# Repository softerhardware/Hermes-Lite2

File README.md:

#Hermes-Lite Ver2 Beta5 Compact Transceiver firmware
[_VU2ZAZ's HL2 Companion board_](https://github.com/bnamnaidu/HL2-Companion-board-codec-and-Filter-)

##Based on the official 20180106 firmware.

##Iambic keyer and audio codec (sidetone)
- [_Keyer function_](https://github.com/ji1udd/Hermes-Lite/blob/6M/audiocodec/docs/Keyer_Sequece_and_setting.pdf)
- Mic gain (AK4951) : Normal 18dB, Boost 30dB
- Enable SPEAKER : [_Re-use "Random"_](https://github.com/ji1udd/Hermes-Lite2/blob/CompactTRX/compact-trx/Keyer_AK4951/docs/Speaker_Setting.jpg) on OpenHPSDR protocol.

##HL2 filter (1 HPF, 6 LPFs) control
- [_Alex / Apollo auto filter mode_](https://github.com/ji1udd/Hermes-Lite2/blob/CompactTRX/compact-trx/TX_RX_Filter/docs/Filter_Setting.jpg) ; HPF and LPFs are switched according to TX and multi RXs frequencies.
- Alex manual filter mode ; This mode is not supported by piHPSDR, but supported by [_PowerSDR_](CTRX_HL2b5/docs/PowerSDR_ALEX_ManualFilter_setting_for_Jims_Filter.jpg).
- Short switch latency for CW keyer operation.
- HPF is bypassed during TX.

##External amplifier band control
- Send TX frequency with Elecraft serial command "FA(VFO A frequency)" to ExtAMP.
- UART 9600bps
- Tested with HARDROCK-50
- UART RxD is not used.

##External ATU control
- Enable ATU : Use [_"Apollo auto tune"_](https://github.com/ji1udd/Hermes-Lite2/blob/CompactTRX/compact-trx/powercontrol/docs/ATU_Setting.jpg) on OpenHPSDR protocol.
- Send START trigger to ATU (like Start SW), Receive STATUS from ATU (like Tuning LED).
- [_Control sequence_](https://github.com/ji1udd/Hermes-Lite2/blob/CompactTRX/compact-trx/powercontrol/docs/ATU_timing_chart.jpg)
- Tested with ICOM AH-4

##LED Ports
- The function is automatically selected by ExtAMP/ExtATU interface circuit installation on board.

##Others
- Embedded PA is always enabled for a stand alone transceiver.

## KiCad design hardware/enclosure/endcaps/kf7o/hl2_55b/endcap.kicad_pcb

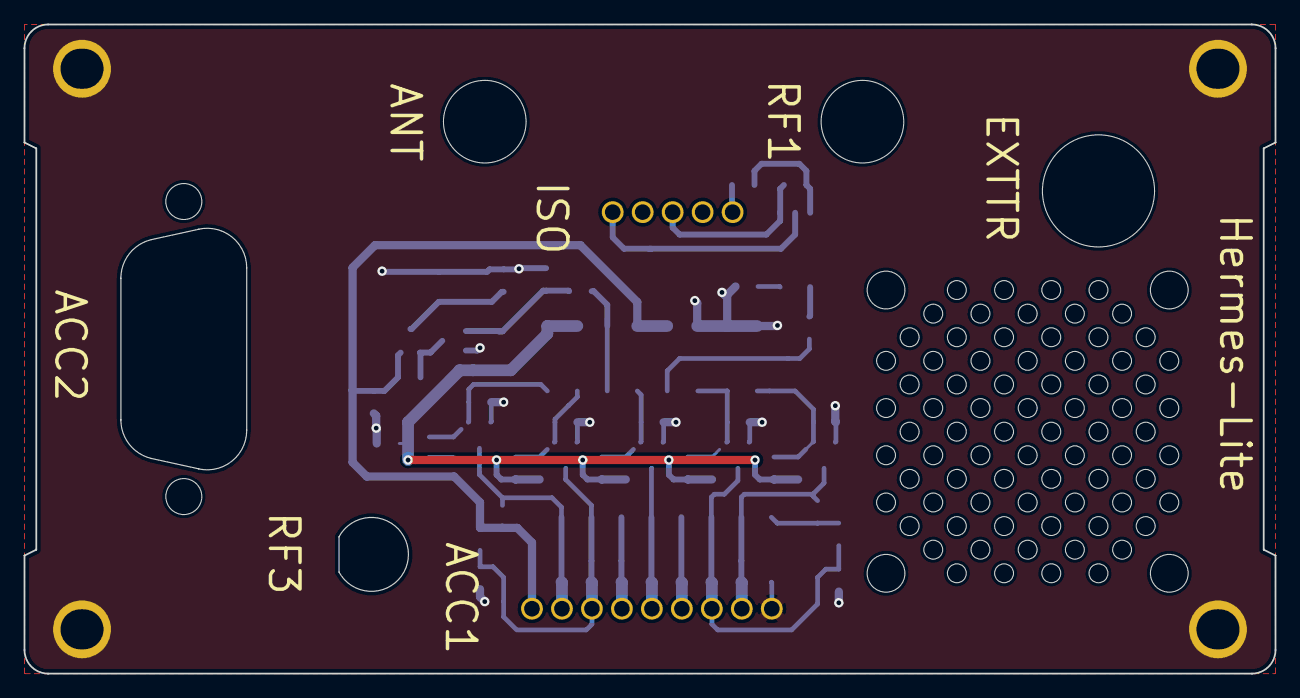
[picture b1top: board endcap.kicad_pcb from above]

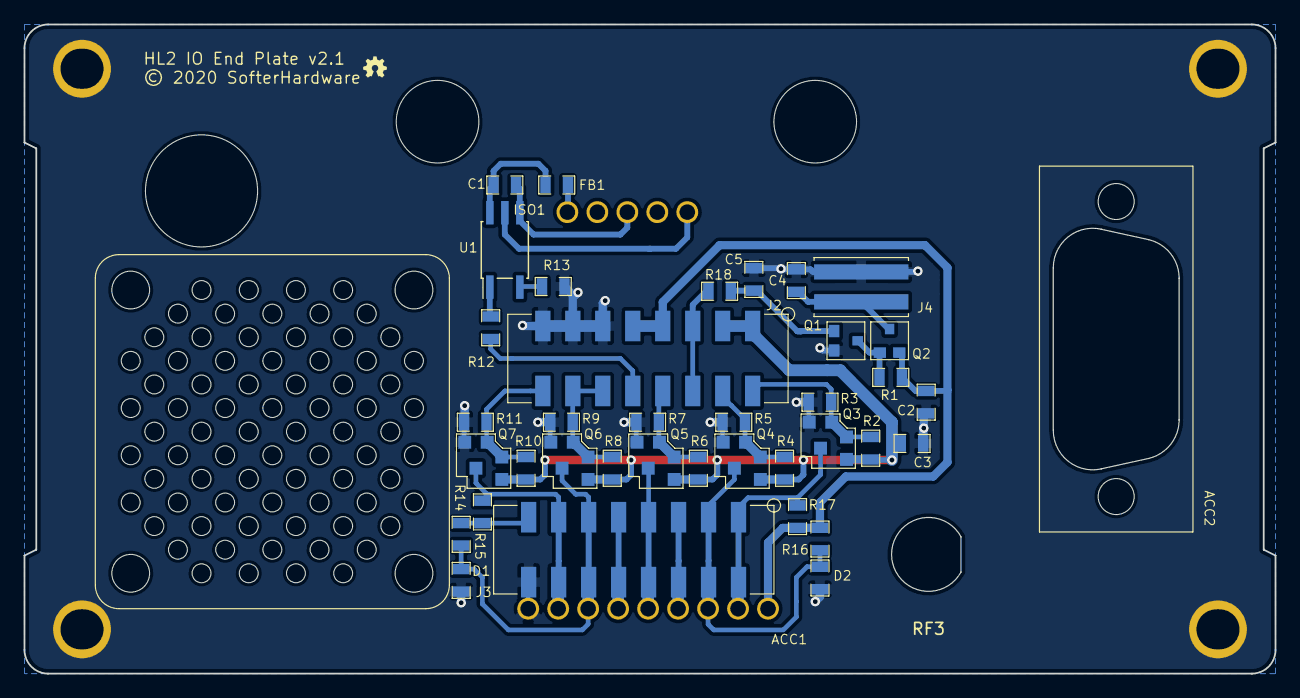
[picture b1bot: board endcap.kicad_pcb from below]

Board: 2 copper layers, 106.0 x 55.0 mm, 45 parts (41 on the bottom side), 27 nets.

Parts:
ACC1: Terminal Block; terminal_block
ACC2: DB9; db9inside
C1, C2, C3, C4, C5: 0.1uF; SMD-0805
D1, D2: 1N4148; SMD-0805
FB1: Ferrite_Bead_Small; SMD-0805
ISO1: Terminal Block; terminal_block5
J2, J3: Male Header; male_header
J4: Fan; male_header_2
MH1, MH2, MH3, MH4: 3mm; mh3mm
Q1: DTC144E; SOT23_3
Q2: IRLML6402; SOT23_3
Q3, Q4, Q5, Q6, Q7: MULTIFET; 3sot3_3
R1, R2, R3, R4, R5, R6, R7, R8, R9, R10, R11, R14, R15, R16, R17: 10K; SMD-0805
R12, R18: 1K; SMD-0805
R13: 680; SMD-0805
RF3: SMA; sma_panel
U1: ACPL-M21L-000E; SO-5_4.4x3.6mm_P1.27mm

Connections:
GNDS: ACC1.9, C2.1, C3.2, C4.1, C5.1, D1.2, D2.2, J2.11, J2.13, J2.15, J3.16, J4.2, MH1.1, MH2.1, MH3.1, MH4.1, Q1.2, Q3.2, Q4.2, Q5.2, Q6.2, Q7.2, R3.2, R5.2, R7.2, R9.2, R11.2, R13.2
ISOIN: J2.10, R12.2
unnamed: ACC1.2, J3.1, J3.2, Q3.3, R17.2
unnamed: ACC1.3, D2.1, J3.3, J3.4, Q4.3, R16.2
unnamed: ACC1.4, J3.5, J3.6
unnamed: ACC1.5, J3.7, J3.8, Q5.3
unnamed: ACC1.6, J3.9, J3.10
unnamed: ACC1.7, D1.1, J3.11, J3.12, Q6.3, R15.1
unnamed: ACC1.8, J3.13, J3.14, Q7.3, R14.1
unnamed: C1.1, FB1.2, U1.6
unnamed: C1.2, ISO1.3, U1.4
unnamed: C4.2, J4.1, Q2.3
unnamed: C5.2, Q1.1, R18.2
unnamed: FB1.1, ISO1.1
unnamed: ISO1.5, U1.5
unnamed: J2.2, Q3.1, R2.2, R3.1
unnamed: J2.4, Q4.1, R4.2, R5.1
unnamed: J2.5, J2.6, R18.1
unnamed: J2.8, Q5.1, R6.2, R7.1
unnamed: J2.12, J2.14, Q6.1, R8.2, R9.1
unnamed: J2.16, Q7.1, R10.2, R11.1
unnamed: J3.15, R14.2, R15.2
unnamed: Q1.3, Q2.1, R1.2
unnamed: R12.1, U1.1
unnamed: R13.1, U1.3
VSUP: ACC1.1, C2.2, J2.7, J2.9, Q2.2, R1.1, R16.1, R17.1
Vlvds: C3.1, J2.1, J2.3, Q3.4, Q4.4, Q5.4, Q6.4, Q7.4, R2.1, R4.1, R6.1, R8.1, R10.1

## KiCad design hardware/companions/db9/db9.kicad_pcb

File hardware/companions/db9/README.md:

# BOM

The BOM below lists possible options for the DB9 adapter board. The builder should choose what components they need to buy and install.

| Reference | Quantity | Component |
| --------- | -------- | --------- |
| J3 | 1 | [DB-9 male](https://www.digikey.com/product-detail/en/edac-inc/627-009-220-047/151-1197-ND/1298747) |
| Q1, Q2 | 2 | [BSS138](https://www.digikey.com/product-detail/en/micro-commercial-co/BSS138W-TP/BSS138W-TPMSCT-ND/6616168) |
| R1, R2 | 2 | [10K 0805](https://www.digikey.com/product-detail/en/yageo/RC0805FR-0710KL/311-10.0KCRCT-ND/730482) |
| J1, J2, J4 | 1 | [5x2 male header](https://www.digikey.com/product-detail/en/sullins-connector-solutions/PRPC005DAAN-RC/S2011EC-05-ND/2775289) |

# Assembly

Please refer to the [schematic](db9.pdf) during assembly. Please refer to the HR50 interface notes found on the [IO wiki page](https://github.com/softerhardware/Hermes-Lite2/wiki/IO#io-boards) for details on how to use this with the HR50.

Below is a picture of an assembled DB-9 IO board. Only one of the level shifter channels is installed, TX on pin 3 of the DB-9. This is all the that HR50 requires. The other level shifter can be installed if RX is required.

This assembly assumes a crossover cable. Install TX on the channel to the DB-9 pin 2 if a straight through cable is used.

The level shifter portion of the PCB can be broken off and jumpers to extra IO channels on the end plate can be used used instead. It is recommended to use the level shifters on the small DB-9 IO board, and the option to break the board may be removed in the future.

## Connection Diagram

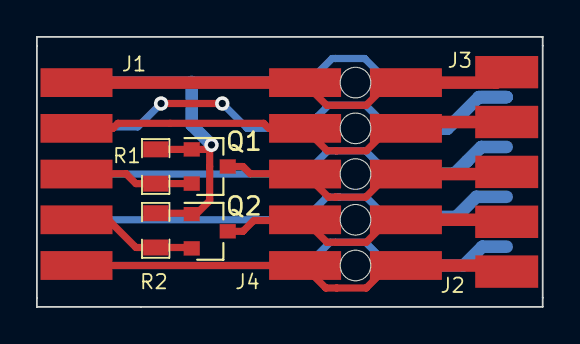
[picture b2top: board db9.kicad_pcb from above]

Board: 2 copper layers, 28.1 x 15.0 mm, 9 parts (0 on the bottom side), 12 nets.

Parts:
B1: break10
J1, J2, J4: edge10
J3: DB9_Male; db9edge
Q1, Q2: BSS138; SOT-23
R1, R2: 10K; SMD-0805

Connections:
GNDS: J1.5, J2.5, J3.5, J4.5
unnamed: J1.1, J2.1, J3.1, J4.1
unnamed: J1.2, Q2.2, R2.2
unnamed: J1.3, Q1.2, R1.2
unnamed: J1.4, J2.4, J3.4, J4.4
unnamed: J1.6, J2.6, J3.6, J4.6
unnamed: J1.7, J2.7, J3.7, J4.7
unnamed: J1.8, J2.8, J3.8, J4.8
unnamed: J1.9, J2.9, J3.9, J4.9
unnamed: J2.2, J3.2, J4.2, Q2.3
unnamed: J2.3, J3.3, J4.3, Q1.3
VCC: J1.10, J2.10, J4.10, Q1.1, Q2.1, R1.1, R2.1

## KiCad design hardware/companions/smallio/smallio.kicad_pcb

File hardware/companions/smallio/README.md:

# BOM

The BOM below lists possible options for IO jumper board. The builder should choose what components they need to buy and install.

| Reference | Quantity | Component |
| --------- | -------- | --------- |
| DB1 | 1 | [5x2 male header 2.54mm](https://www.digikey.com/product-detail/en/sullins-connector-solutions/PRPC005DAAN-RC/S2011EC-05-ND) |
| DB17 | 1 | [4x1 male header 2.54mm](https://www.digikey.com/product-detail/en/w-rth-elektronik/61300411121/732-5317-ND) |
| U1 | 1 | [MCP23008T-E-SS](https://www.digikey.com/product-detail/en/microchip-technology/MCP23008T-E-SS/MCP23008T-E-SSCT-ND) |
| C1 | 1 | [0.1uF 0805](https://www.digikey.com/product-detail/en/kemet/C0805C104Z5VACTU/399-1177-1-ND/411452) |
| J1, J2 | 2 | [0Ohm 0805](https://www.digikey.com/product-detail/en/yageo/RC0805JR-070RL/311-0.0ARCT-ND) |

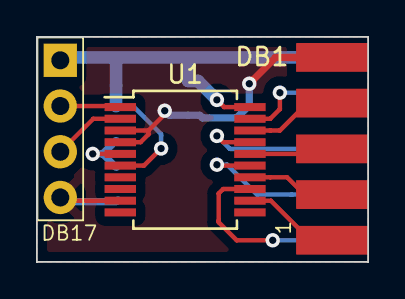
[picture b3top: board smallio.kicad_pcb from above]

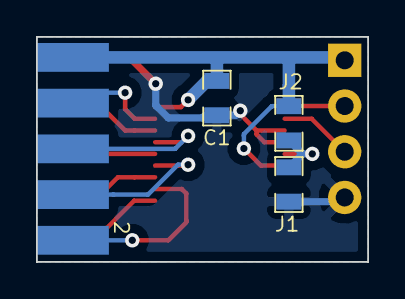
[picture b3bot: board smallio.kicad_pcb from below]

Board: 2 copper layers, 18.4 x 12.5 mm, 6 parts (3 on the bottom side), 13 nets.

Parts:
C1: 0.1uF; SMD-0805
DB1: IO10; edge10_alt
DB17: RFD4d; 4x1
J1, J2: 0; SMD-0805
U1: MCP23008-E_SS; SSOP-20_5.3x7.2mm_P0.65mm

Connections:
GNDS: C1.1, DB1.9, DB17.4, J1.2, U1.3, U1.4, U1.9
unnamed: DB1.1, U1.12
unnamed: DB1.2, U1.13
unnamed: DB1.3, U1.14
unnamed: DB1.4, U1.15
unnamed: DB1.5, U1.16
unnamed: DB1.6, U1.17
unnamed: DB1.7, U1.18
unnamed: DB1.8, U1.19
unnamed: DB17.2, U1.1
unnamed: DB17.3, U1.2
unnamed: J1.1, J2.2, U1.5
VCC: C1.2, DB1.10, DB17.1, J2.1, U1.6, U1.20

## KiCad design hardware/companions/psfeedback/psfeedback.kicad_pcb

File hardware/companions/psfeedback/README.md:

# BOM

The BOM below lists possible options for PureSignal feedback board. The builder should choose what components they need to buy and install.

| Reference | Quantity | Component |
| --------- | -------- | --------- |
| RF1 | 1 | [Edge Launch SMA](https://www.digikey.com/product-detail/en/adam-tech/RF2-04A-T-00-50-G/2057-RF2-04A-T-00-50-G-ND) |
| R1 | 1 | [0Ohm 0805](https://www.digikey.com/product-detail/en/yageo/RC0805JR-070RL/311-0.0ARCT-ND) |
| R2 | 1 | [49.9 0805](https://www.digikey.com/product-detail/en/yageo/RC0805FR-0749R9L/311-49.9CRCT-ND) |
| R3 | 1 | [470 0805](https://www.digikey.com/product-detail/en/yageo/RC0805FR-07470RL/311-470CRCT-ND) |
| R4 | 1 | [1K 0805](https://www.digikey.com/product-detail/en/yageo/RC0805FR-071KL/311-1.00KCRCT-ND) |

# Assembly

Please refer to the [schematic](psfeedback.pdf) during assembly. 

Below is a picture of an assembled PureSignal feedback board soldered on to the HL2/N2ADR jumper board. The components installed are as per the schematic, but experimentation may be necessary to determine the best values. The PCB supports pi and t attenuator configurations. 
[Pi Calculator](https://chemandy.com/calculators/matching-pi-attenuator-calculator.htm)
[T Calculator](https://chemandy.com/calculators/matching-t-attenuator-calculator.htm)

Note that the PCB only connects to one pin on the HL2/N2ADR jumper board. This is so that the connection between the two pins on the HL2/N2ADR jumper board can be drilled open so that less "wire" is hanging off of this line. This can only be done if the feedback board is installed so that it hangs out towards T3. If installed to hang out towards the N2ADR board, then the two pins on the HL2/N2ADR jumper board must remain connected.

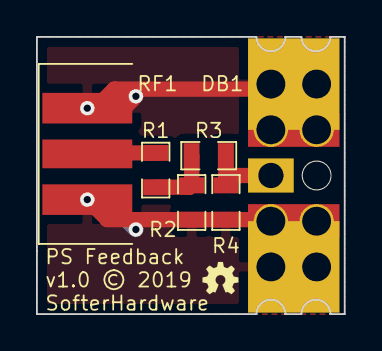
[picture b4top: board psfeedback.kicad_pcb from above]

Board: 2 copper layers, 17.1 x 15.4 mm, 6 parts (0 on the bottom side), 4 nets.

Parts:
DB1: RFD2b; psfeedback
R1: 0; SMD-0805
R2: 50; SMD-0805
R3: 470; SMD-0805
R4: 1K; SMD-0805
RF1: BNC; SMAEDGE

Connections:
GNDS: DB1.2, R2.2, R4.2, RF1.2
unnamed: DB1.1, R3.1, R4.1
unnamed: R1.1, R2.1, R3.2
unnamed: R1.2, RF1.1

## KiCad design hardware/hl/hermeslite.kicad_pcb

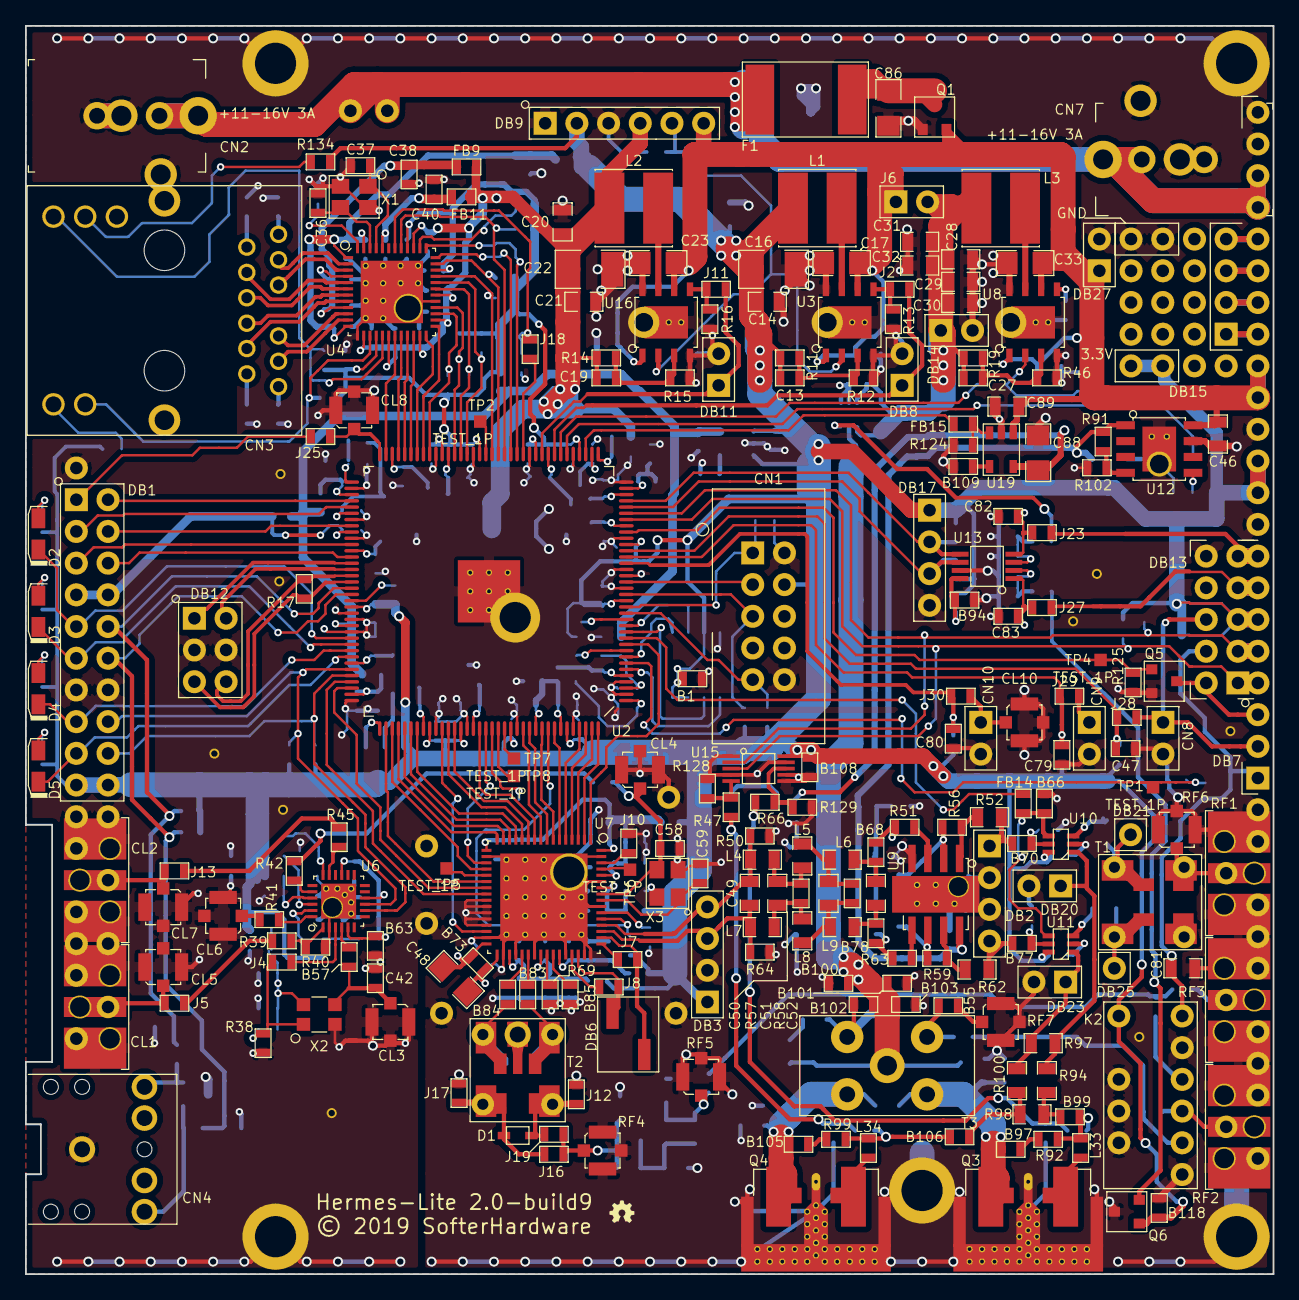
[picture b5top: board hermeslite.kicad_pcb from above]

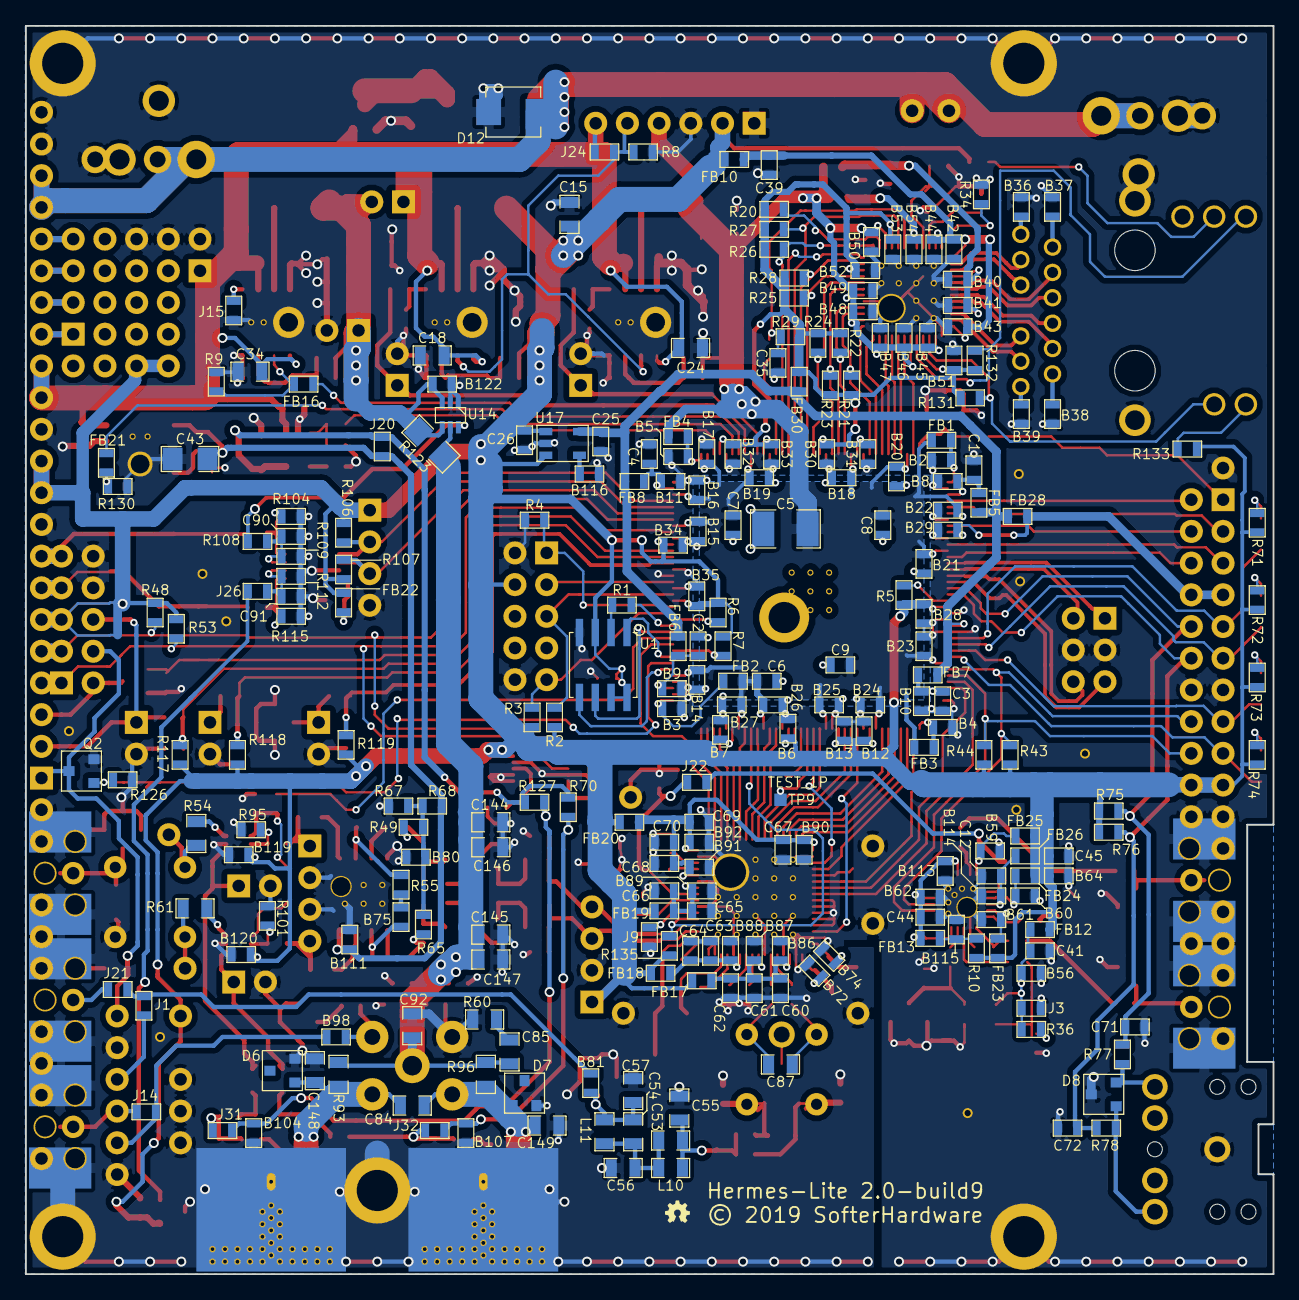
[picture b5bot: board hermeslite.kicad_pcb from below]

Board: 4 copper layers, 99.9 x 100.0 mm, 488 parts (246 on the bottom side), 274 nets.

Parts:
B1, B2, B3, B4, B5, B6, B7, B8, B9, B10, B11, B12, B13, B14, B15, B16, B17, B18, B19, B20, B21, B22, B23, B24, B25, B26, B27, B28, B29, B30, B31, B32, B33, B34, B35, B36, B37, B38, B39, B40, B41, B42, B43, B44, B45, B46, B47, B48, B49, B50, B51, B52, B53, B54, B55, B56, B57, B59, B60, B61, B62, B63, B64, B66, B68, B70, B72, B73, B74, B75, B77, B78, B80, B81, B83, B84, B85, B86, B87, B88, B89, B90, B91, B92, B94, B97, B98, B99, B100, B101, B102, B103, B104, B105, B106, B107, B108, B109, B111, B113, B114, B115, B116, B118, B119, B120, B122: 0.1uF; SMD-0603
C1, C2, C3, C4, C6, C7, C8, C9, C12, C25, C35, C38, C39, C40, C41, C44, C45, C62, C64, C66, C70: 10uF; SMD-0603
C5, C16, C22: 100uF; SMD-1210
C13, C19, C27, C82, C83, C90, C91: 4.7nF; SMD-0603
C14, C15, C20, C21, C28, C29, C30, C31, C32, C92: 22uF; SMD-0805
C17, C23, C33, C43, C48, C86, C88: 10uF; SMD-1206
C18, C24, C34: 4.7uF; SMD-0805
C26, C47, C60, C61, C63, C65, C67, C68, C69, C71, C72, C79, C80: 1uF; SMD-0603
C36, C37, C58, C59: 15pF; SMD-0603
C42: DNI; SMD-0603
C46, C89, C144, C145, C146, C147: 1uF; SMD-0805
C49: 75pF; SMD-0805
C50: 150pF; SMD-0805
C51: 160pF; SMD-0805
C52, C57, C81: 100pF; SMD-0805
C53, C54, C55: 10pF; SMD-0805
C56: 180pF; SMD-0805
C84: 390pF; SMD-0805
C85, C148, C149: 270pF; SMD-0805
C87: 8.2pF; SMD-0805
CL1, CL2: SMA; SMAEDGE_TH_L
CL3, CL4, CL5, CL6, CL7, CL8, CL10: uFL; UFL
CN1: USBBlaster2; USBBLASTER
CN2, CN7: PS; PWRBARREL2
CN3: MagJack; MAGJACK
CN4: STEREO
CN8, CN9, CN10: RFD2b; 2x1
D1: TVS; SOD323
D2, D3, D4, D5: Led_Small; LEDn
D6, D7: DNI; SOT23_3
D8: SM05; SOT23_3
D12: SMBJ18CA; smbj18ca
DB1: IO20; 10x2
DB2, DB3: RFD4d; 4x1
DB6: RFD2b; 2x1smt
DB7: IO22; 22x1
DB8, DB11, DB14, DB20, DB23, DB27: RFD2b; 2x1
DB9: IO6b; 6x1
DB12: IO6b; 3x2
DB13: IO10; 5x2
DB15: IO6b; 4x5
DB17: RFD4b; 4x1
DB21, DB25: DNI; 1x1
F1: 3A@20V; FUSE
FB1, FB2, FB3, FB4, FB5, FB6, FB7, FB8, FB9, FB10, FB11, FB12, FB13, FB14, FB15, FB16, FB17, FB18, FB19, FB20, FB21, FB22, FB23, FB24, FB25, FB26, FB28, FB30: FB; SMD-0603
GT1, GT2, GT3, GT4, GT10, GT11, GT12, GT13, GT14: DNI; GNDTAP
GT5, GT6, GT7, GT8, GT9: DNI; m1d1
J1, J2, J5, J9, J10, J11, J13, J14, J15, J17, J18, J19, J21, J22, J23, J24, J25, J26, J27, J28, J29, J30, J31, J32: JNC; SMD-0603
J3, J4, J7, J8, J12, J16, J20: JNO; SMD-0603
J6: RFD2b; 2x1
K2: NA3WK-K; DPDT_GND
L1, L3: 3.3uH; GENERICPSL
L2: 2.2uH; GENERICPSL
L4, L7: 240nH; SMD-0805
L5, L6, L8, L9: 270nH; SMD-0805
L10, L11: 330nH; SMD-0805
L33, L34: 0nH; SMD-0603
MH1, MH2, MH3, MH4, MH5: DNI; m3
MH6, MH7, MH8: DNI; m1d1
Q1: DMP3099L; SOT23_3
Q2, Q5: NUD3124; SOT23_3
Q3, Q4: LDMOS; COMBORFGNDnohole
Q6: MCP9700; SOT23_3
R1, R41, R42, R45, R50, R64: 33; SMD-0603
R2, R3, R4, R5, R6, R7, R8, R9, R13, R14, R16, R21, R22, R23, R24, R25, R27, R28, R29, R128, R129, R131, R132: 10K; SMD-0603
R10: 2.2; SMD-0603
R11: 35.7K; SMD-0603
R12, R91: 11.5K; SMD-0603
R15: 20K; SMD-0603
R17, R77, R78: 100; SMD-0603
R19: 16.2K; SMD-0603
R20, R26, R49, R65, R75, R76: 2.2K; SMD-0603
R34: 12.1K; SMD-0603
R36, R38: DNI; SMD-0603
R39: 130; SMD-0603
R40: 75; SMD-0603
R43, R44, R48, R53, R95, R101, R106, R107, R117, R118, R119, R124, R125, R126, R130, R135: 4.7K; SMD-0603
R46: 1.8K; SMD-0603
R47, R66: 9.1K; SMD-0603
R51, R63: 22; SMD-0603
R52, R54, R61, R62, R94, R100: 12; SMD-0805
R55: 120; SMD-0603
R56, R59: 330; SMD-0603
R57, R58, R67, R68, R71, R72, R73, R74, R104, R109, R112, R115: 1K; SMD-0603
R60, R93, R96, R97, R98: 1K; SMD-0805
R69, R102: 1.6K; SMD-0603
R70, R127: 27K; SMD-0603
R92, R99, R108, R133, R134: 270; SMD-0603
R123: 0.04; SMD-1206
RF1, RF2: SMA/BNC; SMAEDGE_TH_R
RF3: SMA; SMAEDGE_TH_R
RF4, RF5, RF6, RF7: uFL; UFL
T1: 1:1 Z; TRANSFSMT4
T2: 8:1 Z; TRANSFSMT
T3: 4:1 Z; BN202V
TP1, TP2, TP4, TP5, TP6, TP7, TP8, TP9: TEST_1P; TP
U1: EEPROM; SOIC-8
U2: FPGA; CYCLONEIV
U3, U8, U16: ST1S10
U4: KSZ9031RN; KSZ9031
U6: 5P49V5923; IDTVERSA
U7: AD9866BCPZ; AD9866
U9: OPA2677
U10, U11: PE4259
U12: AP2204; ap2204
U13: MAX11613
U14: INA199A1DC; PE4259
U15: MCP4662; SOIC-10
U17: TPS730; SOT23
U19: LP2985; SOT23
X1: 25MHz; XTAL
X2: 38.4MHz; SMALLOSC
X3: 38.4MHz; XTAL

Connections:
+1V2: B14.1, B15.1, B16.1, B17.1, B18.1, B19.1, B20.1, B21.1, B22.1, B23.1, B24.1, B25.1, B26.1, B27.1, B45.1, B46.1, B47.1, B48.1, B49.1, B50.1, C5.2, C6.2, C7.2, C8.2, C9.2, C19.1, C20.1, C21.1, C22.1, DB9.4, FB1.1, FB2.1, FB3.1, FB4.1, FB9.1, FB11.1, L2.2, R14.1, U2.5, U2.29, U2.34, U2.38, U2.45, U2.61, U2.70, U2.78, U2.84, U2.102, U2.116, U2.124, U2.134, U2.138, U4.14, U4.18, U4.23, U4.26, U4.30, U4.39
+2V5: C25.1, FB5.1, FB6.1, FB7.1, FB8.1, FB28.1, FB30.1, U2.96, U17.5
+3V3: B1.1, B6.1, B7.1, B12.1, B13.1, B28.1, B34.1, B35.1, B64.1, B108.1, B118.1, B119.1, B120.1, C13.1, C14.1, C15.1, C16.1, C26.1, C45.1, CN1.4, DB1.19, DB1.20, DB3.1, DB7.6, DB7.10, DB7.11, DB9.2, DB13.5, DB15.5, DB17.1, FB10.2, FB12.2, FB17.2, FB18.1, FB19.1, FB20.2, FB22.1, FB23.2, FB24.2, FB25.2, FB26.2, K2.1, L1.2, Q6.1, R2.2, R3.2, R5.2, R6.2, R7.2, R10.1, R11.1, R43.1, R44.1, R48.2, R53.2, R71.2, R72.2, R73.2, R74.2, R75.2, R76.2, R106.2, R107.2, R117.2, R118.2, R119.2, R133.2, R134.2, R135.2, U1.3, U1.7, U1.8, U2.17, U2.26, U2.93, U2.117, U2.122, U2.130, U2.139, U10.6, U11.6, U15.10, U17.1, U17.3
+VBIAS: C88.1, J20.1, R70.2, R127.2, U19.5
+VOP: B111.2, C43.1, J20.2, R68.2, R91.1, U9.8, U12.1
+VPA: B122.1, C27.1, C28.1, C29.1, C30.1, C31.1, C32.1, DB14.1, J6.2, L3.2, R19.1, R123.1, U14.3, U14.4
/Ethernet/RXD0: R24.2, U2.58, U4.32
/Ethernet/RXD1: R23.2, U2.59, U4.31
/Ethernet/RXD2: R22.2, U2.60, U4.28
/Ethernet/RXD3: R21.2, U2.64, U4.27
/Ethernet/TXD0: U2.71, U4.19
/Ethernet/TXD1: U2.69, U4.20
/Ethernet/TXD2: U2.68, U4.21
/Ethernet/TXD3: U2.67, U4.22
/Input Output/AIN1: DB7.7, DB13.7, J27.2
/Input Output/AIN2: DB7.8, DB13.9, J23.2
/Input Output/CN8: CN8.1, DB7.2, DB13.6, J28.1
/Input Output/SPR1: DB7.15, DB15.1
/Input Output/SPR2: DB7.16, DB15.2
/Input Output/SPR3: DB7.17, DB15.3
/Input Output/SPR4: DB7.18, DB15.4
/PA/bias0: B104.2, J31.2, R66.2, R127.1
/PA/bias1: B107.2, J32.2, R47.2, R70.1
/Power and FPGA/enpwr: DB9.5, J24.2, R8.1, U3.2, U16.2
/RF Frontend/Vop/2: B80.2, R49.1, R65.2, R67.2, R68.1
EXTTR: DB7.3, DB13.2, Q5.3
GND: B1.2, B2.2, B3.2, B4.2, B5.2, B6.2, B7.2, B8.2, B9.2, B10.2, B11.2, B12.2, B13.2, B14.2, B15.2, B16.2, B17.2, B18.2, B19.2, B20.2, B21.2, B22.2, B23.2, B24.2, B25.2, B26.2, B27.2, B28.2, B29.2, B30.2, B31.2, B32.2, B33.2, B34.2, B35.2, B36.2, B37.2, B38.2, B39.2, B40.2, B41.2, B42.2, B43.2, B44.2, B45.2, B46.2, B47.2, B48.2, B49.2, B50.2, B51.2, B52.2, B53.2, B54.2, B56.2, B59.2, B60.2, B61.2, B62.2, B63.2, B64.2, B66.1, B72.2, B74.2, B80.1, B85.2, B86.2, B87.2, B88.2, B89.2, B90.2, B91.2, B92.2, B94.2, B100.1, B101.1, B102.1, B103.1, B104.1, B107.1, B108.2, B109.2, B111.1, B113.2, B114.2, B115.2, B116.2, B118.2, B119.2, B120.2, B122.2, C1.2, C2.2, C3.2, C4.2, C5.1, C6.1, C7.1, C8.1, C9.1, C12.2, C14.2, C15.2, C16.2, C17.2, C18.2, C20.2, C21.2, C22.2, C23.2, C24.2, C25.2, C26.2, C28.2, C29.2, C30.2, C31.2, C32.2, C33.2, C34.2, C35.2, C36.2, C37.2, C38.2, C39.2, C40.2, C41.2, C42.1, C43.2, C44.2, C45.2, C46.2, C47.2, C55.2, C56.2, C57.2, C58.2, C59.2, C60.2, C61.2, C62.2, C63.2, C64.2, C65.2, C66.2, C67.2, C68.2, C69.2, C70.2, C71.2, C72.2, C79.2, C80.2, C81.2, C82.2, C83.2, C86.2, C88.2, C89.2, C90.2, C91.2, C92.2, C144.2, C145.2, C146.2, C147.2, C148.2, C149.2, CL1.2, CL2.2, CL3.2, CL4.2, CL5.2, CL6.2, CL7.2, CL8.2, CL10.2, CN1.2, CN1.10, CN2.2, CN3.18, CN4.1, CN7.2, CN8.2, CN9.2, CN10.2, D6.2, D7.2, D8.3, D12.2, DB1.13, DB1.14, DB2.2, DB2.3, DB3.2, DB7.9, DB7.12, DB7.21, DB7.22, DB8.2, DB9.1, DB9.3, DB11.2, DB12.3, DB12.4, DB13.8, DB13.10, DB14.2, DB15.6, DB17.4, DB20.2, DB23.2, DB27.2, GT1.1, GT2.1, GT3.1, GT4.1, GT5.1, GT6.1, GT7.1, GT8.1, GT9.1, GT10.1, GT11.1, GT12.1, GT13.1, GT14.1, J3.2, J9.1, J10.1, J12.2, J15.1, J17.1, K2.3, K2.4, K2.5, K2.7, K2.11, MH1.1, MH2.1, MH3.1, MH4.1, MH5.1, MH6.1, Q1.1, Q2.2, Q3.2, Q4.2, Q5.2, Q6.3, R4.2, R8.2, R9.2, R12.2, R13.1, R15.2, R16.1, R34.2, R38.2, R40.2, R46.2, R50.2, R60.1, R64.1, R67.1, R69.1, R95.2, R101.1, R102.1, R104.1, R109.1, R112.1, R115.1, R124.1, R125.1, R126.1, R128.1, R129.1, R130.1, RF1.2, RF2.2, RF3.2, RF4.2, RF5.2, RF6.2, RF7.2, T1.3, T3.4, U1.4, U2.2, U2.4, U2.19, U2.21, U2.22, U2.27, U2.36, U2.41, U2.48, U2.57, U2.63, U2.74, U2.79, U2.82, U2.94, U2.95, U2.97, U2.108, U2.118, U2.123, U2.131, U2.140, U2.145, U3.4, U3.8, U3.9, U4.13, U4.29, U4.49, U6.2, U6.25, U7.18, U7.25, U7.26, U7.27, U7.28, U7.29, U7.31, U7.34, U7.36, U7.39, U7.44, U7.47, U7.48, U7.55, U7.59, U7.63, U7.65, U8.4, U8.8, U8.9, U9.4, U10.2, U11.2, U12.7, U13.7, U14.1, U14.2, U15.1, U15.4, U15.6, U15.7, U15.9, U16.4, U16.8, U16.9, U17.2, U19.2, X1.3, X2.2, X3.3
INTTR: C81.1, DB7.1, DB13.4, K2.12, Q2.3
unnamed: B2.1, FB1.2, U2.73
unnamed: B3.1, FB2.2, U2.1
unnamed: B4.1, FB3.2, U2.109
unnamed: B5.1, FB4.2, U2.37
unnamed: B8.1, C1.1, FB5.2, U2.75
unnamed: B9.1, C2.1, FB6.2, U2.3
unnamed: B10.1, C3.1, FB7.2, U2.107
unnamed: B11.1, C4.1, FB8.2, U2.35
unnamed: B36.1, CN3.12
unnamed: B37.1, CN3.6
unnamed: B38.1, CN3.1
unnamed: B39.1, CN3.7
unnamed: B40.1, B41.1, C38.1, FB9.2, U4.4, U4.9
unnamed: B42.1, B43.1, B44.1, C39.1, FB10.1, U4.1, U4.12, U4.47
unnamed: B54.1, C40.1, FB11.2, U4.44
unnamed: B55.1, B98.2, T3.5
unnamed: B55.2, RF7.1
unnamed: B56.1, C41.1, FB12.1, J3.1, R36.1, X2.4
unnamed: B57.1, C42.2, CL3.1, X2.3
unnamed: B57.2, U6.4
unnamed: B59.1, FB25.1, U6.18
unnamed: B60.1, FB24.1, U6.21
unnamed: B61.1, FB23.1, U6.23
unnamed: B66.2, FB14.1, U10.4, U11.4
unnamed: B68.1, R49.2, R51.2
unnamed: B68.2, C52.1, L6.2
unnamed: B70.1, R95.1, U10.5
unnamed: B70.2, DB2.1, R52.1
unnamed: B72.1, B73.1, C48.1, U7.33
unnamed: B73.2, B74.1, C48.2, U7.32
unnamed: B75.1, R59.2, U9.6
unnamed: B75.2, R55.1
unnamed: B77.1, R101.2, U11.5
unnamed: B77.2, DB2.4, R62.1
unnamed: B78.1, R63.2, R65.1
unnamed: B78.2, C52.2, L9.1
unnamed: B81.1, J1.1, J21.1
unnamed: B81.2, C54.1, C57.1, L11.2, RF5.1
unnamed: B83.1, C87.1, T2.1
unnamed: B83.2, U7.38
unnamed: B84.1, C87.2, T2.3
unnamed: B84.2, U7.37
unnamed: B85.1, U7.42
unnamed: B86.1, B87.1, C60.1, C61.1, C62.1, FB17.1, U7.35, U7.40
unnamed: B88.1, C63.1, C64.1, FB18.2, U7.43
unnamed: B89.1, C65.1, C66.1, FB19.2, U7.58
unnamed: B90.1, B91.1, B92.1, C67.1, C68.1, C69.1, C70.1, FB20.1, U7.17, U7.60, U7.64
unnamed: B94.1, FB22.2, U13.8
unnamed: B97.1, C84.1, C148.1, D6.1, Q3.3, R93.2, T3.1
unnamed: B97.2, R92.1
unnamed: B98.1, J14.2, K2.8
unnamed: B99.1, J31.1, L33.1, R92.2
unnamed: B99.2, R94.1, R98.2
unnamed: B100.2, B101.2, B102.2, B103.2, C85.2, C92.1, C144.1, C145.1, C146.1, C147.1, R93.1, R96.2, R123.2, T3.2, U14.5
unnamed: B105.1, C84.2, C149.1, D7.1, Q4.3, R96.1, T3.3
unnamed: B105.2, R99.1
unnamed: B106.1, J32.1, L34.1, R99.2
unnamed: B106.2, R98.1, R100.1
unnamed: B109.1, U19.4
unnamed: B62.1, B63.1, B113.1, C44.1, FB13.1, U6.5, U6.10, U6.15
unnamed: B114.1, C12.1, FB26.1, U6.22
unnamed: B115.1, FB13.2, R10.2
unnamed: B116.1, U17.4
unnamed: C13.2, R11.2, R12.1, U3.3
unnamed: C19.2, R14.2, R15.1, U16.3
unnamed: C27.2, R19.2, R46.1, U8.3
unnamed: C35.1, J18.1, R29.1, U4.42
unnamed: C36.1, U4.46, X1.2
unnamed: C37.1, U4.45, X1.1
unnamed: C47.1, J28.2, R117.1, U2.25
unnamed: C49.1, DB3.4, L4.1, R50.1, U7.52
unnamed: C49.2, DB3.3, L7.2, R64.2, U7.51
unnamed: C50.1, L4.2, L5.1, R57.2
unnamed: C50.2, L7.1, L8.2, R57.1
unnamed: C51.1, L5.2, L6.1, R58.2
unnamed: C51.2, L8.1, L9.2, R58.1
unnamed: C53.1, C54.2, C56.1, L10.2, L11.1
unnamed: C53.2, C55.1, J16.1, J19.2, L10.1, RF4.1
unnamed: C58.1, CL4.1, J22.2, U7.57, X3.2
unnamed: C59.1, U7.56, X3.1
unnamed: C71.1, DB1.10, R75.1, R77.1, U2.90
unnamed: C72.1, DB1.12, R76.1, R78.1, U2.91
unnamed: C79.1, J29.2, R118.1, U2.24
unnamed: C80.1, J30.2, R119.1, U2.23
unnamed: C82.1, J23.1, R104.2, U13.4
unnamed: C83.1, J27.1, R115.2, U13.1
unnamed: C85.1, R60.2
unnamed: C86.1, F1.2, Q1.3
unnamed: C90.1, R108.1, R109.2, U13.3
unnamed: C91.1, J26.1, R112.2, U13.2
unnamed: CL1.1, CL5.1, J5.1
unnamed: CL2.1, CL7.1, J13.2
unnamed: CL6.1, R41.1
unnamed: CL8.1, J25.1, U2.72
unnamed: CL10.1, CN10.1, J30.1
unnamed: CN1.1, R4.1, U2.16
unnamed: CN1.3, U2.20
unnamed: CN1.5, R2.1, U2.18
unnamed: CN1.9, R3.1, U2.15
unnamed: CN3.2, U4.8
unnamed: CN3.3, U4.7
unnamed: CN3.4, U4.6
unnamed: CN3.5, U4.5
unnamed: CN3.8, U4.11
unnamed: CN3.9, U4.10
unnamed: CN3.10, U4.3
unnamed: CN3.11, U4.2
unnamed: CN3.13, R131.2, U4.15
unnamed: CN3.14, R133.1
unnamed: CN3.16, R134.1
unnamed: CN3.17, R132.2, U4.17
unnamed: CN4.2, D8.1, R78.2
unnamed: CN4.3, D8.2, R77.2
unnamed: CN9.1, J29.1
unnamed: D1.1, J16.2, J17.2, T2.4
unnamed: D1.2, J12.1, J19.1, T2.5
unnamed: D2.1, DB1.9, U2.98
unnamed: D2.2, R71.1
unnamed: D3.1, DB1.11, U2.99
unnamed: D3.2, R72.1
unnamed: D4.1, DB1.15, U2.100
unnamed: D4.2, R73.1
unnamed: D5.1, DB1.17, U2.101
unnamed: D5.2, R74.1
unnamed: DB1.1, J25.2
unnamed: DB1.2, U2.76
unnamed: DB1.3, U2.77
unnamed: DB1.4, U2.80
unnamed: DB1.5, U2.83
unnamed: DB1.6, U2.85
unnamed: DB6.1, J8.1, U7.46
unnamed: DB6.2, J7.1, U7.50
unnamed: DB8.1, J2.2, U2.44
unnamed: DB11.1, J11.2, U2.46
unnamed: DB12.1, U2.86
unnamed: DB12.2, U2.87
unnamed: DB12.5, R17.2, U2.89
unnamed: DB12.6, R17.1, U2.88
unnamed: DB17.2, R106.1, U2.33, U13.5
unnamed: DB17.3, R107.1, U2.32, U13.6
unnamed: DB21.1, R54.1, T1.1
unnamed: DB25.1, R61.1, T1.2
unnamed: FB14.2, U2.11
unnamed: FB15.1, U2.39
unnamed: FB15.2, R124.2, U19.3
unnamed: FB16.1, U2.43
unnamed: FB16.2, R9.1, U8.2
unnamed: FB21.1, U2.42
unnamed: FB21.2, R130.2, U12.5
unnamed: J2.1, R13.2, U3.5
unnamed: J4.1, R36.2, R38.1, X2.1
unnamed: J4.2, U6.3
unnamed: J5.2, R39.2
unnamed: J7.2, U7.49
unnamed: J8.2, U7.45
unnamed: J9.2, U7.54
unnamed: J10.2, U7.62
unnamed: J11.1, R16.2, U16.5
unnamed: J13.1, R45.1
unnamed: J14.1, K2.9, RF2.1
unnamed: J15.2, U8.5
unnamed: J18.2, U2.49
unnamed: J21.2, RF3.1
unnamed: L1.1, U3.7
unnamed: L2.1, U16.7
unnamed: L3.1, U8.7
unnamed: L33.2, Q3.1
unnamed: L34.2, Q4.1
unnamed: Q2.1, R126.2, TP1.1, U2.7
unnamed: Q5.1, R125.2, TP4.1, U2.28
unnamed: R1.1, U1.2
unnamed: R1.2, U2.13
unnamed: R5.1, U2.92
unnamed: R6.1, U2.14
unnamed: R7.1, U2.9
unnamed: R20.2, U4.38
unnamed: R25.2, U2.54, U4.33
unnamed: R26.2, U2.50, U4.37
unnamed: R27.1, U2.52, U4.41
unnamed: R28.1, U2.53, U4.35
unnamed: R34.1, U4.48
unnamed: R39.1, R40.1, U6.1
unnamed: R41.2, U6.24
unnamed: R42.2, U6.20
unnamed: R45.2, U6.17
unnamed: R51.1, U9.3
unnamed: R52.2, R56.1, U9.1
unnamed: R54.2, U10.3
unnamed: R55.2, R56.2, U9.2
unnamed: R59.1, R62.2, U9.7
unnamed: R61.2, U11.3
unnamed: R63.1, U9.5
unnamed: R69.2, U7.41
unnamed: R91.2, R102.2, U12.4
unnamed: R47.1, R128.2, U15.5
unnamed: R66.1, R129.2, U15.8
unnamed: R135.1, U2.136, U7.53
unnamed: RF1.1, RF6.1, T1.4
unnamed: TP2.1, U2.55
unnamed: TP5.1, U7.21
unnamed: TP6.1, U7.61
unnamed: TP7.1, U2.129
unnamed: TP8.1, U2.128
unnamed: TP9.1, U2.127
unnamed: U1.1, U2.8
unnamed: U1.5, U2.6
unnamed: U1.6, U2.12
unnamed: U2.10, U7.1
unnamed: U2.51, U4.36
unnamed: U2.65, U4.25
unnamed: U2.66, U4.24
unnamed: U2.105, U7.24
unnamed: U2.106, U7.23
unnamed: U2.110, U7.22
unnamed: U2.111, U7.20
unnamed: U2.112, U7.16
unnamed: U2.113, U7.15
unnamed: U2.114, U7.14
unnamed: U2.115, U7.13
unnamed: U2.119, U7.30
unnamed: U2.120, U7.12
unnamed: U2.121, U7.11
unnamed: U2.125, U7.10
unnamed: U2.126, U7.19
unnamed: U2.132, U7.9
unnamed: U2.133, U7.8
unnamed: U2.135, U7.7
unnamed: U2.137, U7.6
unnamed: U2.141, U7.5
unnamed: U2.142, U7.4
unnamed: U2.143, U7.3
unnamed: U2.144, U7.2
PATRRX: J1.2, K2.10
RFFE_CLK: J22.1, R42.1
SCL1: DB1.16, R43.2, U2.103, U6.9
SCL2: DB7.5, DB13.3, R48.1, U2.31, U15.2
SDA1: DB1.18, R44.2, U2.104, U6.8
SDA2: DB7.4, DB13.1, R53.1, U2.30, U15.3
TXPAn: DB23.1, R97.1, R100.2, U11.1
TXPAp: DB20.1, R94.2, R97.2, U10.1
VEXT: CN2.1, CN7.1, D12.1, DB7.19, DB7.20, F1.1, MH7.1, MH8.1
VSUP: C17.1, C18.1, C23.1, C24.1, C33.1, C34.1, C46.1, C89.1, DB7.13, DB7.14, DB9.6, DB27.1, J6.1, J24.1, Q1.2, U3.1, U3.6, U8.1, U8.6, U12.8, U16.1, U16.6, U19.1
Veth: B30.1, B31.1, B32.1, B33.1, B51.1, B52.1, B53.1, FB30.2, R20.1, R21.1, R22.1, R23.1, R24.1, R25.1, R26.1, R27.2, R28.2, R29.2, R131.1, R132.1, U2.40, U2.47, U2.56, U2.62, U4.16, U4.34, U4.40
Vipa: R108.2, U14.6
Vlvds: B29.1, DB1.7, DB1.8, FB28.2, U2.81
Vtemp: J26.2, Q6.2

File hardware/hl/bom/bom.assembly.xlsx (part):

Part ID | Description | Part Number | Substitution Okay | Designators | Footprint | Pins | Quantity | Part Reference Link
15331 | 0.1uF 0603>=X5R>=50V<=20% | C0603C104M5RACTU | Y | B1,B2,B3,B4,B5,B6, B7,B8,B9,B10,B11, B12,B13,B14,B15,B16, B17,B18,B19,B20,B21, 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 | 603 | 2 | 112 | http://www.octopart.com/search?q=C0603C104M5RACTU
20411 | 10uF 0603>=X5R>=6.3V<=20% | GRM188R60J106KE47D | Y | C1,C2,C3,C4,C6,C7, C8,C9,C12,C25,C35, C38,C39,C40,C41,C44, C45,C62,C64,C66,C70 | 603 | 2 | 21 | http://www.octopart.com/search?q=GRM188R60J106KE47D
 | 100uF 1206>=X5R>=6.3V<=20% | GRM31CR60J107ME39K | Y | C5,C16,C22 | 1206 | 2 | 3 | http://www.octopart.com/search?q=GRM31CR60J107ME39K
55004 | 4.7nF 0603>=X5R>=25V<=20% | CL10B472KB8NNNC | Y | C13,C19,C27 | 603 | 2 | 3 | http://www.octopart.com/search?q=CL10B472KB8NNNC
46786 | 22uF 0805>=X5R>=16V<=20% | GRM21BR61E226ME44L | Y | C14,C15,C20,C21,C28, C29,C30,C31,C32 | 805 | 2 | 9 | http://www.octopart.com/search?q=GRM21BR61E226ME44L
14236 | 10uF 1206>=X5R>=25V<=20% | CL31A106KAHNNNE | Y | C17,C23,C33,C43,C48, C86,C88 | 1206 | 2 | 7 | http://www.octopart.com/search?q=CL31A106KAHNNNE
2131 | 4.7uF 0805>=X5R>=25V<=20% | GRM21BR61E475KA12L | Y | C18,C24,C34 | 805 | 2 | 3 | http://www.octopart.com/search?q=GRM21BR61E475KA12L
16531 | 1uF 0603>=X5R>=6.3V<=20% | GRM188R61E105KA12D | Y | C26,C60,C61,C63,C65, C67,C68,C69,C71,C72, C73,C74 | 603 | 2 | 12 | http://www.octopart.com/search?q=GRM188R61E105KA12D
1996 | 15pF 0603NP0>=6.3V<=5% | CC0603JRNPO9BN150 | Y | C36,C37 | 603 | 2 | 2 | http://www.octopart.com/search?q=CC0603JRNPO9BN150
29074 | 1uF 0805>=X5R>=25V<=20% | CL21B105KAFNNNE | Y | C46,C89,C144,C145, C146,C147 | 805 | 2 | 6 | http://www.octopart.com/search?q=CL21B105KAFNNNE
 | 75pF 0805NP0>=50V<=5% | C0805C750J1GACTU | Y | C49 | 805 | 2 | 1 | http://www.octopart.com/search?q=C0805C750J1GACTU
 | 150pF 0805NP0>=50V<=5% | CC0805JRNPO0BN151 | Y | C50 | 805 | 2 | 1 | http://www.octopart.com/search?q=CC0805JRNPO0BN151
 | 160pF 0805NP0>=50V<=5% | GRM2165C2A161JA01D | Y | C51 | 805 | 2 | 1 | http://www.octopart.com/search?q=GRM2165C2A161JA01D
2142 | 100pF 0805NP0>=50V<=5% | CC0805JRNPO0BN101 | Y | C52,C57,C81 | 805 | 2 | 3 | http://www.octopart.com/search?q=CC0805JRNPO0BN101
2137 | 10pF 0805NP0>=50V<=5% | CC0805JRNPO9BN100 | Y | C53 | 805 | 2 | 1 | http://www.octopart.com/search?q=CC0805JRNPO9BN100
 | 180pF 0805NP0>=50V<=5% | CC0805JRNPO0BN181 | Y | C56 | 805 | 2 | 1 | http://www.octopart.com/search?q=CC0805JRNPO0BN181
 | 270pF 0805NP0>=50V<=5% | CC0805JRNPO0BN271 | Y | C84 | 805 | 2 | 1 | http://www.octopart.com/search?q=CC0805JRNPO0BN271
 | 8.2pF 0805NP0>=25V<=5% | CL21C8R2DBANNNC | Y | C87 | 805 | 2 | 1 | http://www.octopart.com/search?q=CL21C8R2DBANNNC
 | 2x5 M 0.1in | 67997-410HLF | Y | CN1 | Custom | 10 | 1 | http://www.octopart.com/search?q=67997-410HLF
 | Eth MagJack | L829-1J1T-43 | N | CN3 | Custom | 18 | 1 | http://www.octopart.com/search?q=L829-1J1T-43
 | TVS Diode | CDSOD323-T05LC | N | D1 | SC-76, SOD-323 | 2 | 1 | http://www.octopart.com/search?q=CDSOD323-T05LC
 | LED RA | LTST-S220KFKT | N | D2,D3,D4,D5 | 2.1x1.0mmRightAngle | 2 | 4 | http://www.octopart.com/search?q=LTST-S220KFKT
 | Schottky Barrier Diode | 1N5711WS-7-F | N | D10,D11 | SC-76, SOD-323 | 2 | 2 | http://www.octopart.com/search?q=1N5711WS-7-F
 | TVS Diode | SMBJ18CA | N | D12 | DO-214AA (SMB) | 2 | 1 | http://www.aliexpress.com/wholesale?SearchText=SMBJ18CA
 | FUSE PTC 3.0A 24V | MF-LSMF300/24X-2 | N | F1 | 2920 7.36x5.12mm | 2 | 1 | http://www.aliexpress.com/wholesale?SearchText=MF-LSMF300/24X-2
 | Ferrite Bead 0603 >= 600 Ohms at 100MHz <= 200 mOhms at DC 1A <=25% | MPZ1608S601ATA00 | Y | FB1,FB2,FB3,FB4,FB5, FB6,FB7,FB8,FB9,FB10, FB11,FB12,FB13,FB14, FB15,FB16,FB17,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 | 603 | 2 | 27 | http://www.octopart.com/search?q=MPZ1608S601ATA00
21903 | 0Ohm 0603<=5%>=1/10W | RC0603JR-070RL | Y | J1,J2,J9,J10,J11, J14,J15,J19,J21,J22, J28,J30,J31,J32,L33, L34 | 603 | 2 | 16 | http://www.octopart.com/search?q=RC0603JR-070RL
 | 3.3uH >=2.4A | SRN5020-3R3M | N | L1,L3 | 5x5mm | 2 | 2 | http://www.octopart.com/search?q=SRN5020-3R3M
 | 2.2uH >=2.4A | SRN5020-2R2Y | N | L2 | 5x5mm | 2 | 1 | http://www.octopart.com/search?q=SRN5020-2R2Y
 | 240nH | LQW2BASR24J00L | N | L4,L7 | 805 | 2 | 2 | http://www.octopart.com/search?q=LQW2BASR24J00L
 | 270nH | LQW2BASR27J00L | N | L5,L6,L8,L9 | 805 | 2 | 4 | http://www.octopart.com/search?q=LQW2BASR27J00L
 | 330nH | LQW2BASR33J00L | N | L10,L11 | 805 | 2 | 2 | http://www.octopart.com/search?q=LQW2BASR33J00L
 | MOSFET P-CH 30V | DMP3099L-7 | N | Q1 | SOT-23-3 | 3 | 1 | http://www.octopart.com/search?q=DMP3099L-7
 | Inductive Load Driver | NUD3124LT1G | N | Q2,Q5 | SOT-23-3 | 3 | 2 | http://www.aliexpress.com/wholesale?SearchText=NUD3124LT1G
 | RF LDMOS | AFT05MS003NT1 | N | Q3,Q4 | SOT-89-3 | 3 | 2 | http://www.octopart.com/search?q=AFT05MS003NT1
 | Thermal Sensor | MCP9700T-E/TT | N | Q6 | SOT-23-3 | 3 | 1 | http://www.aliexpress.com/wholesale?SearchText=MCP9700T-E/TT
23867 | 33 0603<=1%>=1/10W | RC0603FR-0733RL | Y | R1,R42,R50,R64 | 603 | 2 | 4 | http://www.octopart.com/search?q=RC0603FR-0733RL
26547 | 10K 0603<=5%>=1/10W | RC0603FR-0710KL | Y | R2,R3,R4,R5,R6,R7, R14,R21,R22,R23,R24, R25,R27,R28,R29 | 603 | 2 | 15 | http://www.octopart.com/search?q=RC0603FR-0710KL
23666 | 2.2 0603<=5%>=1/10W | RC0603FR-072R2L | Y | R10 | 603 | 2 | 1 | http://www.octopart.com/search?q=RC0603FR-072R2L
 | 35.7K 0603<=1%>=1/10W | RC0603FR-0735K7L | Y | R11 | 603 | 2 | 1 | http://www.octopart.com/search?q=RC0603FR-0735K7L
 | 11.5K 0603<=1%>=1/10W | RC0603FR-0711K5L | Y | R12,R91 | 603 | 2 | 2 | http://www.octopart.com/search?q=RC0603FR-0711K5L
4591 | 20K 0603<=1%>=1/10W | RC0603FR-0720KL | Y | R15 | 603 | 2 | 1 | http://www.octopart.com/search?q=RC0603FR-0720KL
 | 16.2K 0603<=1%>=1/10W | RC0603FR-0716K2L | Y | R19 | 603 | 2 | 1 | http://www.octopart.com/search?q=RC0603FR-0716K2L
4597 | 2.2K 0603<=5%>=1/10W | RC0603FR-072K2L | Y | R20,R26,R49,R65,R75, R76,R79,R80 | 603 | 2 | 8 | http://www.octopart.com/search?q=RC0603FR-072K2L
23693 | 270 0603<=5%>=1/10W | RC0603FR-07270RL | Y | R30,R31,R92,R99 | 603 | 2 | 4 | http://www.octopart.com/search?q=RC0603FR-07270RL
21904 | 1K 0603<=5%>=1/10W | RC0603FR-071KL | Y | R32,R33,R57,R58,R67, R68,R71,R72,R73,R74, R103,R108,R111,R114 | 603 | 2 | 14 | http://www.octopart.com/search?q=RC0603FR-071KL
 | 12.1K 0603<=1%>=1/10W | RC0603FR-0712K1L | Y | R34 | 603 | 2 | 1 | http://www.octopart.com/search?q=RC0603FR-0712K1L
23889 | 4.7K 0603<=5%>=1/10W | RC0603FR-074K7L | Y | R43,R44,R48,R53,R106, R107,R124,R125,R126, R130 | 603 | 2 | 10 | http://www.octopart.com/search?q=RC0603FR-074K7L
4584 | 1.8K 0603<=1%>=1/10W | RC0603FR-071K8L | Y | R46,R104,R115 | 603 | 2 | 3 | http://www.octopart.com/search?q=RC0603FR-071K8L
23987 | 9.1K 0603<=1%>=1/10W | RC0603FR-079K1L | Y | R47,R66 | 603 | 2 | 2 | http://www.octopart.com/search?q=RC0603FR-079K1L
24078 | 22 0603<=5%>=1/10W | RC0603FR-0722RL | Y | R51,R63 | 603 | 2 | 2 | http://www.octopart.com/search?q=RC0603FR-0722RL
 | 12 0805<=5%>=1/8W | RC0805FR-0712RL | Y | R52,R54,R61,R62,R94, R100 | 805 | 2 | 6 | http://www.octopart.com/search?q=RC0805FR-0712RL
4682 | 75 0603<=5%>=1/10W | RC0603FR-0775RL | Y | R55 | 603 | 2 | 1 | http://www.octopart.com/search?q=RC0603FR-0775RL
23865 | 330 0603<=1%>=1/10W | RC0603FR-07330RL | Y | R56,R59 | 603 | 2 | 2 | http://www.octopart.com/search?q=RC0603FR-07330RL
 | 1.6K 0603<=5%>=1/10W | RC0603FR-071K6L | Y | R69,R102 | 603 | 2 | 2 | http://www.octopart.com/search?q=RC0603FR-071K6L
23694 | 27K 0603<=1%>=1/10W | RC0603FR-0727KL | Y | R70,R127 | 603 | 2 | 2 | http://www.octopart.com/search?q=RC0603FR-0727KL
23502 | 100 0603<=1%>=1/10W | RC0603FR-07100RL | Y | R77,R78,R81,R82,R120, R121,R122 | 603 | 2 | 7 | http://www.octopart.com/search?q=RC0603FR-07100RL
23688 | 220K 0603<=1%>=1/10W | RC0603FR-07220KL | Y | R113,R116 | 603 | 2 | 2 | http://www.octopart.com/search?q=RC0603FR-07220KL
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

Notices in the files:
hardware/companions/n2adr/n2adr.kicad_pcb:
Rev E5b9 © 2019 by N2ADR
hardware/companions/psfeedback/psfeedback.kicad_pcb:
v1.0 © 2019
hardware/enclosure/endcaps/kf7o/hl2_55b/endcap.kicad_pcb:
© 2020 SofterHardware
hardware/hl/hermeslite.kicad_pcb:
© 2019 SofterHardware
